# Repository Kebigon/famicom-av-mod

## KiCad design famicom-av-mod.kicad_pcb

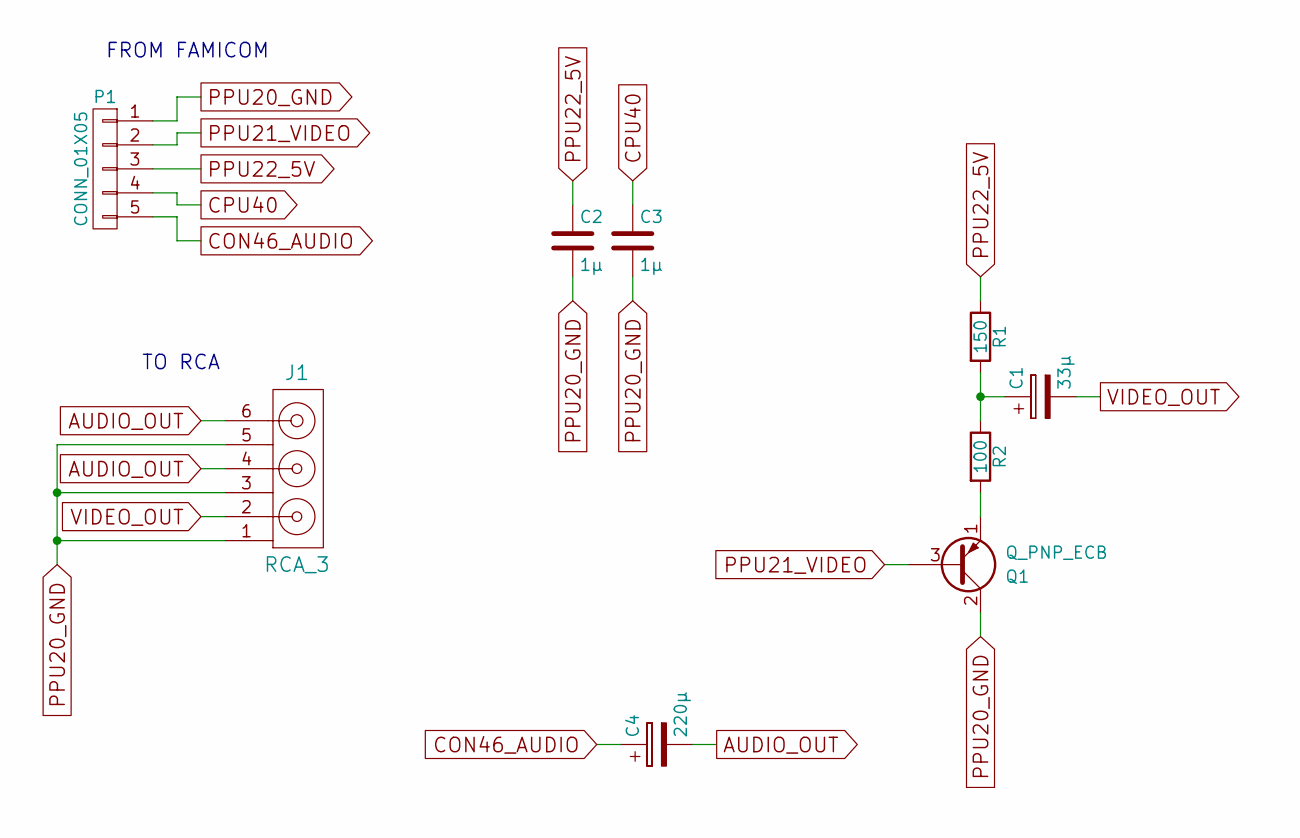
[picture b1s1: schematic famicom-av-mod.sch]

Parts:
C1: 33µ; CP_Radial_Tantal_D4.5mm_P2.50mm
C2, C3: 1µ; C_Disc_D3.0mm_W1.6mm_P2.50mm
C4: 220µ; CP_Radial_Tantal_D4.5mm_P2.50mm
J1: RCA_3; Pin_Header_Straight_1x06_Pitch2.54mm
P1: CONN_01X05; Pin_Header_Straight_1x05_Pitch2.54mm
Q1: Q_PNP_ECB; Pin_Header_Straight_1x03_Pitch2.54mm
R1: 150; R3
R2: 100; R3

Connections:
AUDIO_OUT: C4.2, J1.4, J1.6
CON46_AUDIO: C4.1, P1.5
CPU40: C3.1, P1.4
unnamed: C1.1, R1.2, R2.1
unnamed: Q1.1 (E), R2.2
PPU20_GND: C2.2, C3.2, J1.1, J1.3, J1.5, P1.1, Q1.2 (C)
PPU21_VIDEO: P1.2, Q1.3 (B)
PPU22_5V: C2.1, P1.3, R1.1
VIDEO_OUT: C1.2, J1.2

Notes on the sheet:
FROM FAMICOM
TO RCA

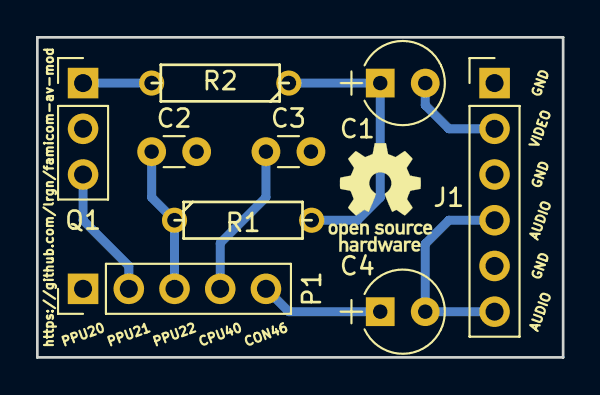
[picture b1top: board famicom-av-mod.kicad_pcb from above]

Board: 2 copper layers, 29.2 x 17.8 mm, 9 parts (0 on the bottom side), 9 nets.

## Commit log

2017-06-25 Version 0.1
2017-06-29 Moving labels to F.SilkS layer
2017-06-29 Also export edges on gerber file
